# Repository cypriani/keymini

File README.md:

# Keymini, a minimalist ergonomic keyboard

> Perfection is achieved, not when there is nothing more to add, but
> when there is nothing left to take away. ― Antoine de Saint-Exupéry

## Presentation

Keymini is a monoblock ergonomic keyboard with 36 keys. It is as low as
possible (with Kailh Choc v1 switches). As it is flat on the underside,
it can be used placed on a laptop keyboard, without actuating the
laptop keyboard keys.

Keymini is a minimalist keyboard in a lot of way:
* Only a keyboard, no LED, no rotary encoder, no screen, not split, no
  hotswap… Just USB-C connector and keys.
* Minimal size, entering in a C5/6 envelope (3 fold A4) or a Nintendo
  Switch Lite case.
* Minimal number of keys, at 36, as popularized by
  [Miryoku](https://github.com/manna-harbour/miryoku).
* Minimal keyspacing, following the classical "choc spacing."
* Minimal height, with the switch plate at 5.8 mm from the desk.
* Minimal number of component, with only 2 extended parts for PCB
  assembly by JLCPCB.
* Minimalistic style, with no decoration, simple hull countour.
* Minimalist license (MIT) for an opensource keyboard.

Inspirations:
* My previous designs, in particular
  [KeySeeBee](https://github.com/TeXitoi/keyseebee) for the components
  and the fat plate, and
  [Keyberon-f4](https://github.com/TeXitoi/keyberon-f4) for
  experiencing with the key placement and unibody shape.
* [Ferris](https://github.com/pierrechevalier83/ferris) for the
  stagger and the diode placement..
* [3W6](https://github.com/weteor/3W6) for the "too fat plate" design
  idea, and gluing something directly on the back of the PCB.

## Other pages to see

To see more photos, see the [gallery](GALLERY.md).

You can look at the [build guide](BUILDING.md), to see how it is
constructed, and to make your own!

For instructions on the PCB manufacturing, see the [gerbers
directory](pcb/gerbers/).

For information on building and flashing the firmware, see the
[firmware directory](firmware/).

For information on the default layout, see the [layout page](LAYOUT.md).

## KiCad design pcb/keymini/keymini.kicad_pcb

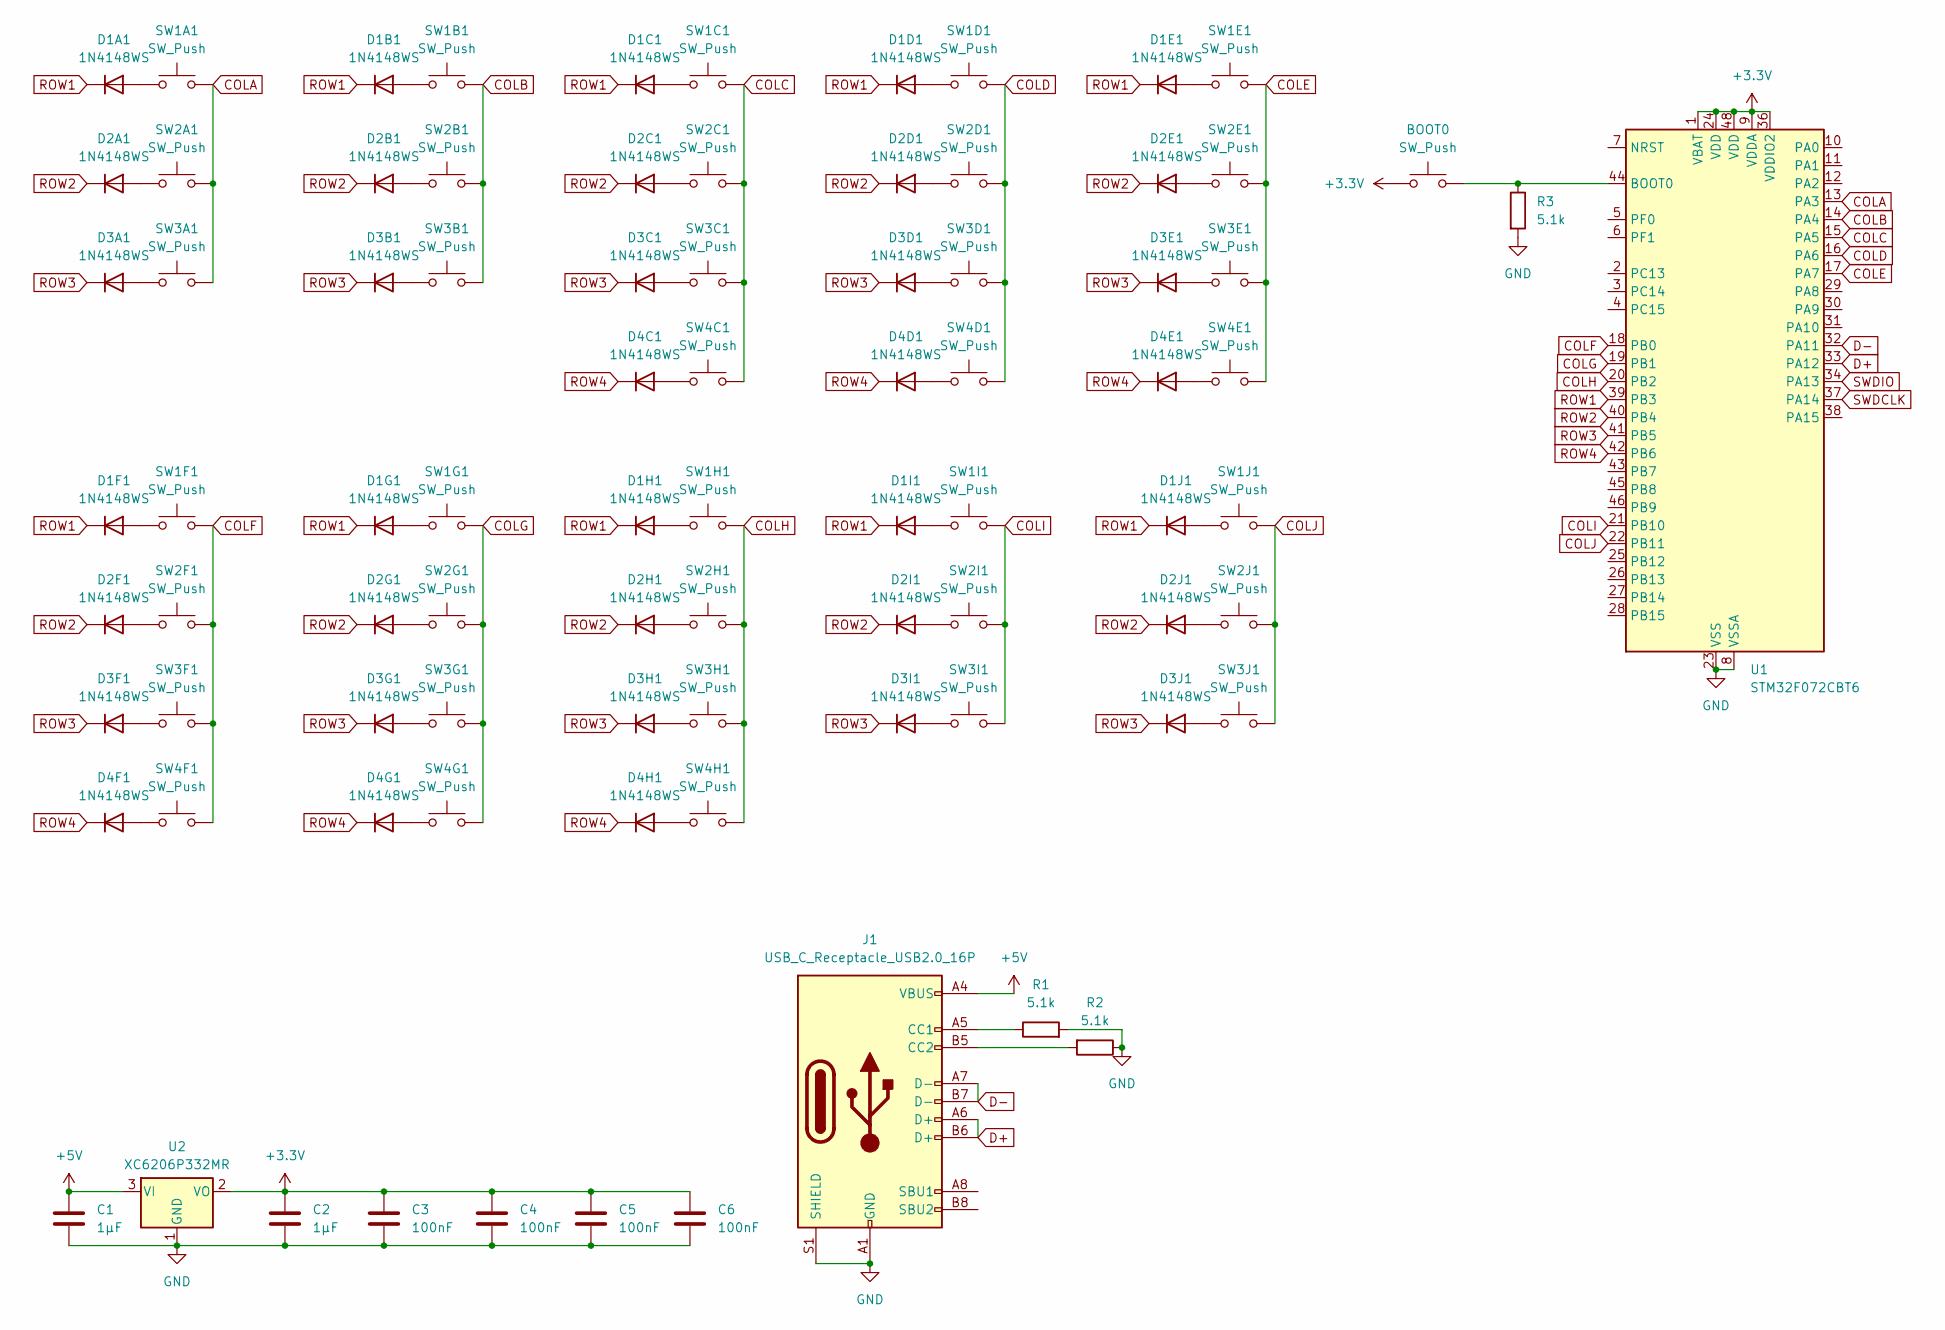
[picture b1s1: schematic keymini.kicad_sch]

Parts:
BOOT0: SW_Push; SW_SPST_CK_RS282G05A3
C1, C2: 1µF; C_0805_2012Metric
C3, C4, C5, C6: 100nF; C_0805_2012Metric
D1A1, D1B1, D1C1, D1D1, D1E1, D1F1, D1G1, D1H1, D1I1, D1J1, D2A1, D2B1, D2C1, D2D1, D2E1, D2F1, D2G1, D2H1, D2I1, D2J1, D3A1, D3B1, D3C1, D3D1, D3E1, D3F1, D3G1, D3H1, D3I1, D3J1, D4C1, D4D1, D4E1, D4F1, D4G1, D4H1: 1N4148WS; D_SOD-323
J1: USB_C_Receptacle_USB2.0_16P; USB_C_Receptacle_HRO_TYPE-C-31-M-12
R1, R2, R3: 5.1k; R_0805_2012Metric
SW1A1, SW1B1, SW1C1, SW1D1, SW1E1, SW1F1, SW1G1, SW1H1, SW1I1, SW1J1, SW2A1, SW2B1, SW2C1, SW2D1, SW2E1, SW2F1, SW2G1, SW2H1, SW2I1, SW2J1, SW3A1, SW3B1, SW3C1, SW3D1, SW3E1, SW3F1, SW3G1, SW3H1, SW3I1, SW3J1, SW4C1, SW4D1, SW4E1, SW4F1, SW4G1, SW4H1: SW_Push; SW_PG1350
U1: STM32F072CBT6; LQFP-48_7x7mm_P0.5mm
U2: XC6206P332MR; SOT-23-3

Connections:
+3.3V: BOOT0.1, C2.1, C3.1, C4.1, C5.1, C6.1, U1.1 (VBAT), U1.9 (VDDA), U1.24 (VDD), U1.36 (VDDIO2), U1.48 (VDD), U2.2 (VO)
+5V: C1.2, J1.A4 (VBUS), J1.A9 (VBUS), J1.B4 (VBUS), J1.B9 (VBUS), U2.3 (VI)
COLA: SW1A1.2, SW2A1.2, SW3A1.2, U1.13 (PA3)
COLB: SW1B1.2, SW2B1.2, SW3B1.2, U1.14 (PA4)
COLC: SW1C1.2, SW2C1.2, SW3C1.2, SW4C1.2, U1.15 (PA5)
COLD: SW1D1.2, SW2D1.2, SW3D1.2, SW4D1.2, U1.16 (PA6)
COLE: SW1E1.2, SW2E1.2, SW3E1.2, SW4E1.2, U1.17 (PA7)
COLF: SW1F1.2, SW2F1.2, SW3F1.2, SW4F1.2, U1.18 (PB0)
COLG: SW1G1.2, SW2G1.2, SW3G1.2, SW4G1.2, U1.19 (PB1)
COLH: SW1H1.2, SW2H1.2, SW3H1.2, SW4H1.2, U1.20 (PB2)
COLI: SW1I1.2, SW2I1.2, SW3I1.2, U1.21 (PB10)
COLJ: SW1J1.2, SW2J1.2, SW3J1.2, U1.22 (PB11)
D+: J1.A6 (D+), J1.B6 (D+), U1.33 (PA12)
D-: J1.A7 (D-), J1.B7 (D-), U1.32 (PA11)
GND: C1.1, C2.2, C3.2, C4.2, C5.2, C6.2, J1.A1 (GND), J1.A12 (GND), J1.B1 (GND), J1.B12 (GND), J1.S1 (SHIELD), R1.2, R2.1, R3.2, U1.8 (VSSA), U1.23 (VSS), U1.35 (VSS), U1.47 (VSS), U2.1 (GND)
unnamed: D1A1.2 (A), SW1A1.1
unnamed: D1B1.2 (A), SW1B1.1
unnamed: D1C1.2 (A), SW1C1.1
unnamed: D1D1.2 (A), SW1D1.1
unnamed: D1E1.2 (A), SW1E1.1
unnamed: D1F1.2 (A), SW1F1.1
unnamed: D1G1.2 (A), SW1G1.1
unnamed: D1H1.2 (A), SW1H1.1
unnamed: D1I1.2 (A), SW1I1.1
unnamed: D1J1.2 (A), SW1J1.1
unnamed: D2A1.2 (A), SW2A1.1
unnamed: D2B1.2 (A), SW2B1.1
unnamed: D2C1.2 (A), SW2C1.1
unnamed: D2D1.2 (A), SW2D1.1
unnamed: D2E1.2 (A), SW2E1.1
unnamed: D2F1.2 (A), SW2F1.1
unnamed: D2G1.2 (A), SW2G1.1
unnamed: D2H1.2 (A), SW2H1.1
unnamed: D2I1.2 (A), SW2I1.1
unnamed: D2J1.2 (A), SW2J1.1
unnamed: D3A1.2 (A), SW3A1.1
unnamed: D3B1.2 (A), SW3B1.1
unnamed: D3C1.2 (A), SW3C1.1
unnamed: D3D1.2 (A), SW3D1.1
unnamed: D3E1.2 (A), SW3E1.1
unnamed: D3F1.2 (A), SW3F1.1
unnamed: D3G1.2 (A), SW3G1.1
unnamed: D3H1.2 (A), SW3H1.1
unnamed: D3I1.2 (A), SW3I1.1
unnamed: D3J1.2 (A), SW3J1.1
unnamed: D4C1.2 (A), SW4C1.1
unnamed: D4D1.2 (A), SW4D1.1
unnamed: D4E1.2 (A), SW4E1.1
unnamed: D4F1.2 (A), SW4F1.1
unnamed: D4G1.2 (A), SW4G1.1
unnamed: D4H1.2 (A), SW4H1.1
unnamed: J1.A5 (CC1), R1.1
unnamed: J1.B5 (CC2), R2.2
unnamed: BOOT0.2, R3.1, U1.44 (BOOT0)
ROW1: D1A1.1 (K), D1B1.1 (K), D1C1.1 (K), D1D1.1 (K), D1E1.1 (K), D1F1.1 (K), D1G1.1 (K), D1H1.1 (K), D1I1.1 (K), D1J1.1 (K), U1.39 (PB3)
ROW2: D2A1.1 (K), D2B1.1 (K), D2C1.1 (K), D2D1.1 (K), D2E1.1 (K), D2F1.1 (K), D2G1.1 (K), D2H1.1 (K), D2I1.1 (K), D2J1.1 (K), U1.40 (PB4)
ROW3: D3A1.1 (K), D3B1.1 (K), D3C1.1 (K), D3D1.1 (K), D3E1.1 (K), D3F1.1 (K), D3G1.1 (K), D3H1.1 (K), D3I1.1 (K), D3J1.1 (K), U1.41 (PB5)
ROW4: D4C1.1 (K), D4D1.1 (K), D4E1.1 (K), D4F1.1 (K), D4G1.1 (K), D4H1.1 (K), U1.42 (PB6)
SWDCLK: U1.37 (PA14)
SWDIO: U1.34 (PA13)

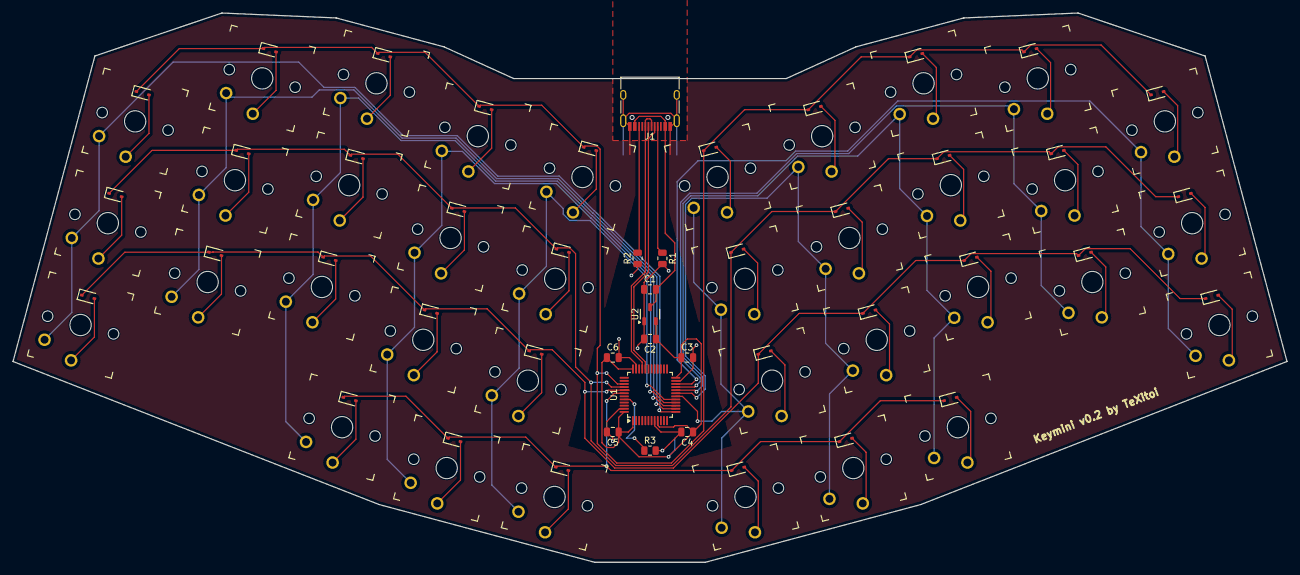
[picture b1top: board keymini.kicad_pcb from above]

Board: 2 copper layers, 205.4 x 88.6 mm, 85 parts (1 on the bottom side), 58 nets.

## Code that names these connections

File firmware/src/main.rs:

#![no_main]
#![no_std]

// set the panic handler
use panic_halt as _;

use crate::layout::{LAYERS, NUM_LAYERS};
use core::convert::Infallible;
use core::mem::MaybeUninit;
use cortex_m::peripheral::SCB;
use hal::gpio::{Input, Output, Pin, PullUp, PushPull};
use hal::prelude::*;
use hal::usb;
use hal::{stm32, timers};
use keyberon::debounce::Debouncer;
use keyberon::key_code::KbHidReport;
use keyberon::layout::{CustomEvent, Layout};
use keyberon::matrix::Matrix;
use rtic::app;
use stm32f0xx_hal as hal;
use usb_device::bus::UsbBusAllocator;
use usb_device::class::UsbClass as _;
use usb_device::device::UsbDeviceState;

mod layout;

type UsbClass = keyberon::Class<'static, usb::UsbBusType, ()>;
type UsbDevice = usb_device::device::UsbDevice<'static, usb::UsbBusType>;

#[link_section = ".uninit.GOTO_BOOTLOADER"]
static mut GOTO_BOOTLOADER: MaybeUninit<u8> = MaybeUninit::uninit();
const GO: u8 = 60;

#[cortex_m_rt::pre_init]
unsafe fn maybe_jump_bootloader() {
    let software_reset = (*hal::pac::RCC::ptr()).csr.read().sftrstf().bit_is_set();
    let jump_bootloader = software_reset && GOTO_BOOTLOADER.assume_init() == GO;
    (*&raw mut GOTO_BOOTLOADER).write(0);
    if jump_bootloader {
        cortex_m::asm::bootload(0x1FFFC800 as _);
    }
}

pub fn bootloader() -> ! {
    unsafe { (*&raw mut GOTO_BOOTLOADER).write(GO) };
    SCB::sys_reset()
}

trait ResultExt<T> {
    fn get(self) -> T;
}
impl<T> ResultExt<T> for Result<T, Infallible> {
    fn get(self) -> T {
        match self {
            Ok(v) => v,
            Err(e) => match e {},
        }
    }
}

#[app(device = crate::hal::pac, peripherals = true, dispatchers = [CEC_CAN])]
mod app {
    use super::*;

    #[shared]
    struct Shared {
        usb_dev: UsbDevice,
        usb_class: UsbClass,
    }

    #[local]
    struct Local {
        matrix: Matrix<Pin<Input<PullUp>>, Pin<Output<PushPull>>, 10, 4>,
        debouncer: Debouncer<[[bool; 10]; 4]>,
        layout: Layout<10, 4, NUM_LAYERS, ()>,
        timer: timers::Timer<stm32::TIM3>,
    }

    #[init(local = [bus: Option<UsbBusAllocator<usb::UsbBusType>> = None])]
    fn init(mut c: init::Context) -> (Shared, Local, init::Monotonics) {
        let mut rcc = c
            .device
            .RCC
            .configure()
            .hsi48()
            .enable_crs(c.device.CRS)
            .sysclk(48.mhz())
            .pclk(24.mhz())
            .freeze(&mut c.device.FLASH);

        let gpioa = c.device.GPIOA.split(&mut rcc);
        let gpiob = c.device.GPIOB.split(&mut rcc);

        let usb = usb::Peripheral {
            usb: c.device.USB,
            pin_dm: gpioa.pa11,
            pin_dp: gpioa.pa12,
        };
        *c.local.bus = Some(usb::UsbBusType::new(usb));
        let usb_bus = c.local.bus.as_ref().unwrap();

        let usb_class = keyberon::new_class(usb_bus, ());
        let usb_dev = keyberon::new_device(usb_bus);

        let mut timer = timers::Timer::tim3(c.device.TIM3, 1.khz(), &mut rcc);
        timer.listen(timers::Event::TimeOut);

        let pa3 = gpioa.pa3;
        let pa4 = gpioa.pa4;
        let pa5 = gpioa.pa5;
        let pa6 = gpioa.pa6;
        let pa7 = gpioa.pa7;
        let Ok(matrix) = cortex_m::interrupt::free(move |cs| {
            Matrix::new(
                [
                    pa3.into_pull_up_input(cs).downgrade(),
                    pa4.into_pull_up_input(cs).downgrade(),
                    pa5.into_pull_up_input(cs).downgrade(),
                    pa6.into_pull_up_input(cs).downgrade(),
                    pa7.into_pull_up_input(cs).downgrade(),
                    gpiob.pb0.into_pull_up_input(cs).downgrade(),
                    gpiob.pb1.into_pull_up_input(cs).downgrade(),
                    gpiob.pb2.into_pull_up_input(cs).downgrade(),
                    gpiob.pb10.into_pull_up_input(cs).downgrade(),
                    gpiob.pb11.into_pull_up_input(cs).downgrade(),
                ],
                [
                    gpiob.pb3.into_push_pull_output(cs).downgrade(),
                    gpiob.pb4.into_push_pull_output(cs).downgrade(),
                    gpiob.pb5.into_push_pull_output(cs).downgrade(),
                    gpiob.pb6.into_push_pull_output(cs).downgrade(),
                ],
            )
        });

        (
            Shared { usb_dev, usb_class },
            Local {
                timer,
                debouncer: Debouncer::new([[false; 10]; 4], [[false; 10]; 4], 5),
                matrix: matrix,
                layout: Layout::new(&LAYERS),
            },
            init::Monotonics(),
        )
    }

    #[task(binds = USB, priority = 2, shared = [usb_dev, usb_class])]
    fn usb_rx(c: usb_rx::Context) {
        (c.shared.usb_dev, c.shared.usb_class).lock(|usb_dev, usb_class| {
            if usb_dev.poll(&mut [usb_class]) {
                usb_class.poll();
            }
        });
    }

    #[task(
        binds = TIM3,
        priority = 1,
        local = [matrix, debouncer, timer, layout],
        shared = [usb_dev, usb_class],
    )]
    fn tick(mut c: tick::Context) {
        let _ = c.local.timer.wait();

        for event in c.local.debouncer.events(c.local.matrix.get().get()) {
            c.local.layout.event(event)
        }

        match c.local.layout.tick() {
            CustomEvent::Release(()) => bootloader(),
            _ => (),
        }
        if c.shared.usb_dev.lock(|d| d.state()) != UsbDeviceState::Configured {
            return;
        }
        let report: KbHidReport = c.local.layout.keycodes().collect();
        if !c
            .shared
            .usb_class
            .lock(|k| k.device_mut().set_keyboard_report(report.clone()))
        {
            return;
        }
        while let Ok(0) = c.shared.usb_class.lock(|k| k.write(report.as_bytes())) {}
    }
}

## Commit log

2024-10-28 PCB schema
2024-10-28 begining of cad
2024-10-29 more cad
2024-10-29 bigger tolerences
2024-10-30 Switch placement
2024-10-30 correct C legend placement
2024-10-31 key_placement.csv
2024-10-31 key placement corrections
2024-10-31 A bit of diode placement
2024-10-31 more diode placement
2024-10-31 diode placement: all done
2024-10-31 composant placement
2024-10-31 rename switches and diodes
2024-10-31 diode check
2024-10-31 a lot of traces
2024-10-31 rows and cols connected
2024-10-31 trace tweeks
2024-11-01 component plate pocket + components on PCB
2024-11-01 Add SWD connector
2024-11-01 complete rooting with swo and ground plate
2024-11-01 Tweeks
2024-11-01 correct usb-c port rounding
2024-11-01 printable plate
2024-11-02 make PCB checker happy
2024-11-03 parameter for usbc connector pocket
2024-11-03 Add gerber
2024-11-03 bom and pos begining
2024-11-03 bom and pos
2024-11-04 Correct switch placement
2024-11-04 update ground plate
2024-11-04 firmware
2024-11-06 Add README.md
2024-11-06 v0.1
2024-11-11 Plate tunning
2024-11-11 JLCPCB instructions
2024-11-11 Add README.md in firmware/
2024-11-11 Corrections
2024-11-19 plate tweeks
2024-11-19 v0.1 report
2024-11-21 Add gallery and remarks about v0.1
2024-11-21 Add no hotswap in README.md
2024-11-21 Add mostly unused keys
2024-11-22 layout tweeks
2024-11-26 Add inspirations
2024-11-26 Add C-BS in the nav layer
2024-11-28 change usb-c pocket in the plate to a simple cut
2024-12-07 Add copper ground pur on front
2024-12-07 Remove SWD connector
2024-12-07 v0.2 gerber
2024-12-08 Remove swd pocker from plate
2024-12-08 More precise non pour around the components
2024-12-08 firmware: remove warnings
2024-12-15 Explain more carefully how to put the keyboard in DFU mode.
2024-12-17 Corrections on pcb/gerbers/README.md
2024-12-25 Add plate.svg
2024-12-28 Add fat plate with visible components as STL
2024-12-29 CNC 1.5mm min rounding files
2024-12-29 Move dogbone
2024-12-31 Smaller component pocket
2025-01-01 smaller component pocket in the freecad version
2025-01-02 Application on thumb for compose
2025-01-04 NUM_LAYER defined one time in layout.rs
2025-01-04 HRM as inverted T
2025-01-12 v0.2
2025-01-14 Add GALLERY.md
2025-01-18 Add BUILDING.md (draft)
2025-01-18 BUILDING: Solder switches
2025-01-19 Update BOM
2025-01-19 BUILDING: leveling the board
2025-01-19 More BUILDING.md
2025-01-22 toolchain installation fix in firmware/README.md
2025-01-23 GALLERY: add Louis’ Keymini
2025-01-30 Layout description
2025-02-19 Add images, move layout to its page
2025-03-18 Put Tab on home row index
2025-03-21 First try at customizing layout
2025-03-21 firmware/README: fixed a few typos
2025-04-02 Tweek usb-c pocket in CNC file
2025-05-10 Approach Arsenik + media layer
2025-05-10 Switched top/bottom right-hand nav rows
2025-05-10 Nav minor reorg + Alt-Tab
